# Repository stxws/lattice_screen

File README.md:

玩的点阵屏

hardware：硬件设计
software：软件程序

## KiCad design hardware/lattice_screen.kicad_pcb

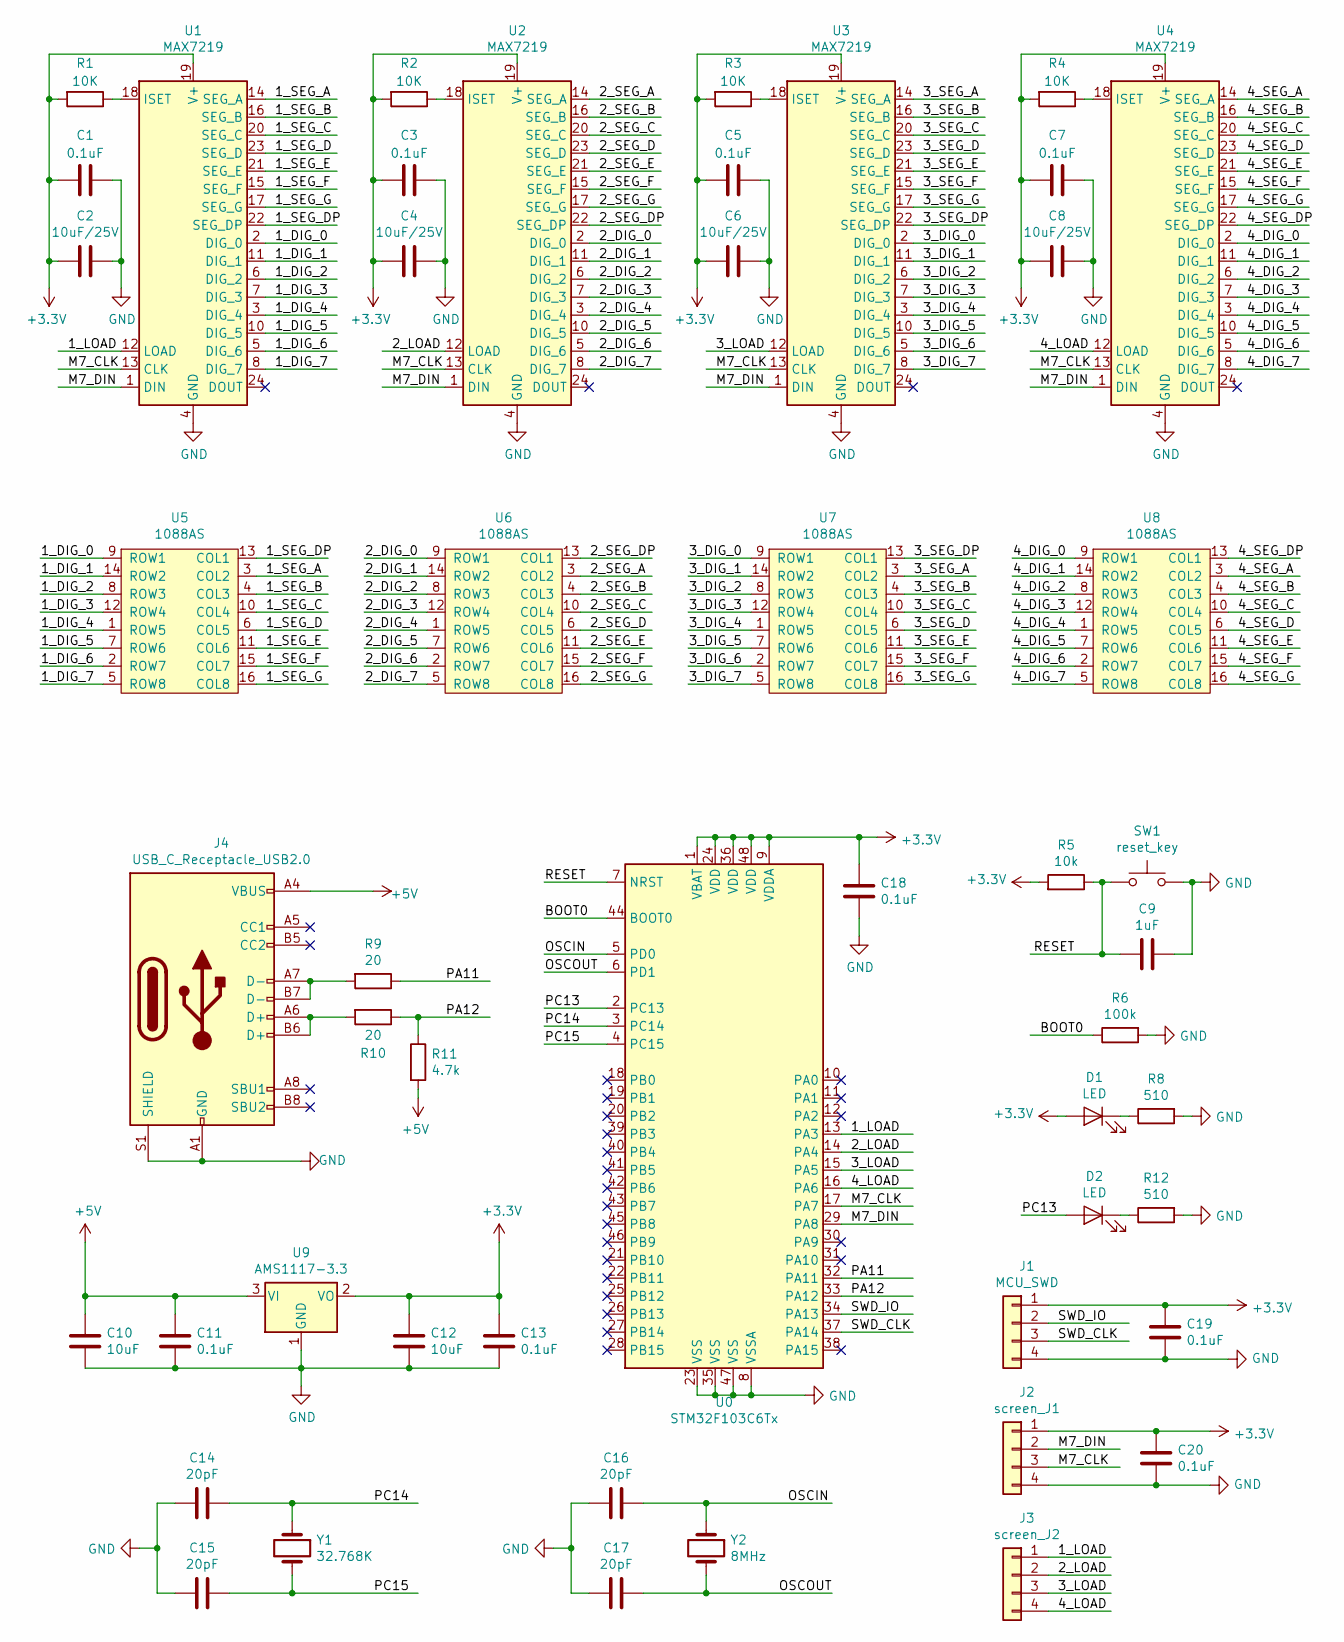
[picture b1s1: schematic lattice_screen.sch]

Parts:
C1, C3, C5, C7, C11, C13, C18, C19, C20: 0.1uF; R_0603_1608Metric_Pad1.05x0.95mm_HandSolder
C2, C4, C6, C8: 10uF/25V; R_0603_1608Metric_Pad1.05x0.95mm_HandSolder
C9: 1uF; R_0603_1608Metric_Pad1.05x0.95mm_HandSolder
C10, C12: 10uF; R_0603_1608Metric_Pad1.05x0.95mm_HandSolder
C14, C15, C16, C17: 20pF; R_0603_1608Metric_Pad1.05x0.95mm_HandSolder
D1, D2: LED; R_0805_2012Metric_Pad1.15x1.40mm_HandSolder
J1: MCU_SWD; PinHeader_1x04_P2.54mm_Horizontal
J2: screen_J1; PinHeader_1x04_P2.54mm_Horizontal
J3: screen_J2; PinHeader_1x04_P2.54mm_Horizontal
J4: USB_C_Receptacle_USB2.0; USB_C_Receptacle_HRO_TYPE-C-31-M-12
R1, R2, R3, R4: 10K; R_0603_1608Metric_Pad1.05x0.95mm_HandSolder
R5: 10k; R_0603_1608Metric_Pad1.05x0.95mm_HandSolder
R6: 100k; R_0603_1608Metric_Pad1.05x0.95mm_HandSolder
R8, R12: 510; R_0603_1608Metric_Pad1.05x0.95mm_HandSolder
R9, R10: 20; R_0603_1608Metric_Pad1.05x0.95mm_HandSolder
R11: 4.7k; R_0603_1608Metric_Pad1.05x0.95mm_HandSolder
SW1: reset_key; SW_SPST_CK_RS282G05A3
U0: STM32F103C6Tx; LQFP-48_7x7mm_P0.5mm
U1, U2, U3, U4: MAX7219; SOP-24_7.5x15.4mm_P1.27mm
U5, U6, U7, U8: 1088AS
U9: AMS1117-3.3; SOT-223-3_TabPin2
Y1: 32.768K; Crystal_DS26_D2.0mm_L6.0mm_Horizontal
Y2: 8MHz; Crystal_HC49-4H_Vertical

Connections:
+3V3: C1.2, C2.2, C3.2, C4.2, C5.2, C6.2, C7.2, C8.2, C12.1, C13.1, C18.1, C19.1, C20.1, D1.2 (A), J1.1, J2.1, R1.2, R2.2, R3.2, R4.2, R5.2, U0.1 (VBAT), U0.9 (VDDA), U0.24 (VDD), U0.36 (VDD), U0.48 (VDD), U1.19 (V+), U2.19 (V+), U3.19 (V+), U4.19 (V+), U9.2 (VO)
+5V: C10.1, C11.1, J4.A4 (VBUS), J4.A9 (VBUS), J4.B4 (VBUS), J4.B9 (VBUS), R11.2, U9.3 (VI)
/1_DIG_0: U1.2 (DIG_0), U5.9 (ROW1)
/1_DIG_1: U1.11 (DIG_1), U5.14 (ROW2)
/1_DIG_2: U1.6 (DIG_2), U5.8 (ROW3)
/1_DIG_3: U1.7 (DIG_3), U5.12 (ROW4)
/1_DIG_4: U1.3 (DIG_4), U5.1 (ROW5)
/1_DIG_5: U1.10 (DIG_5), U5.7 (ROW6)
/1_DIG_6: U1.5 (DIG_6), U5.2 (ROW7)
/1_DIG_7: U1.8 (DIG_7), U5.5 (ROW8)
/1_LOAD: J3.1, U0.13 (PA3), U1.12 (LOAD)
/1_SEG_A: U1.14 (SEG_A), U5.3 (COL2)
/1_SEG_B: U1.16 (SEG_B), U5.4 (COL3)
/1_SEG_C: U1.20 (SEG_C), U5.10 (COL4)
/1_SEG_D: U1.23 (SEG_D), U5.6 (COL5)
/1_SEG_DP: U1.22 (SEG_DP), U5.13 (COL1)
/1_SEG_E: U1.21 (SEG_E), U5.11 (COL6)
/1_SEG_F: U1.15 (SEG_F), U5.15 (COL7)
/1_SEG_G: U1.17 (SEG_G), U5.16 (COL8)
/2_DIG_0: U2.2 (DIG_0), U6.9 (ROW1)
/2_DIG_1: U2.11 (DIG_1), U6.14 (ROW2)
/2_DIG_2: U2.6 (DIG_2), U6.8 (ROW3)
/2_DIG_3: U2.7 (DIG_3), U6.12 (ROW4)
/2_DIG_4: U2.3 (DIG_4), U6.1 (ROW5)
/2_DIG_5: U2.10 (DIG_5), U6.7 (ROW6)
/2_DIG_6: U2.5 (DIG_6), U6.2 (ROW7)
/2_DIG_7: U2.8 (DIG_7), U6.5 (ROW8)
/2_LOAD: J3.2, U0.14 (PA4), U2.12 (LOAD)
/2_SEG_A: U2.14 (SEG_A), U6.3 (COL2)
/2_SEG_B: U2.16 (SEG_B), U6.4 (COL3)
/2_SEG_C: U2.20 (SEG_C), U6.10 (COL4)
/2_SEG_D: U2.23 (SEG_D), U6.6 (COL5)
/2_SEG_DP: U2.22 (SEG_DP), U6.13 (COL1)
/2_SEG_E: U2.21 (SEG_E), U6.11 (COL6)
/2_SEG_F: U2.15 (SEG_F), U6.15 (COL7)
/2_SEG_G: U2.17 (SEG_G), U6.16 (COL8)
/3_DIG_0: U3.2 (DIG_0), U7.9 (ROW1)
/3_DIG_1: U3.11 (DIG_1), U7.14 (ROW2)
/3_DIG_2: U3.6 (DIG_2), U7.8 (ROW3)
/3_DIG_3: U3.7 (DIG_3), U7.12 (ROW4)
/3_DIG_4: U3.3 (DIG_4), U7.1 (ROW5)
/3_DIG_5: U3.10 (DIG_5), U7.7 (ROW6)
/3_DIG_6: U3.5 (DIG_6), U7.2 (ROW7)
/3_DIG_7: U3.8 (DIG_7), U7.5 (ROW8)
/3_LOAD: J3.3, U0.15 (PA5), U3.12 (LOAD)
/3_SEG_A: U3.14 (SEG_A), U7.3 (COL2)
/3_SEG_B: U3.16 (SEG_B), U7.4 (COL3)
/3_SEG_C: U3.20 (SEG_C), U7.10 (COL4)
/3_SEG_D: U3.23 (SEG_D), U7.6 (COL5)
/3_SEG_DP: U3.22 (SEG_DP), U7.13 (COL1)
/3_SEG_E: U3.21 (SEG_E), U7.11 (COL6)
/3_SEG_F: U3.15 (SEG_F), U7.15 (COL7)
/3_SEG_G: U3.17 (SEG_G), U7.16 (COL8)
/4_DIG_0: U4.2 (DIG_0), U8.9 (ROW1)
/4_DIG_1: U4.11 (DIG_1), U8.14 (ROW2)
/4_DIG_2: U4.6 (DIG_2), U8.8 (ROW3)
/4_DIG_3: U4.7 (DIG_3), U8.12 (ROW4)
/4_DIG_4: U4.3 (DIG_4), U8.1 (ROW5)
/4_DIG_5: U4.10 (DIG_5), U8.7 (ROW6)
/4_DIG_6: U4.5 (DIG_6), U8.2 (ROW7)
/4_DIG_7: U4.8 (DIG_7), U8.5 (ROW8)
/4_LOAD: J3.4, U0.16 (PA6), U4.12 (LOAD)
/4_SEG_A: U4.14 (SEG_A), U8.3 (COL2)
/4_SEG_B: U4.16 (SEG_B), U8.4 (COL3)
/4_SEG_C: U4.20 (SEG_C), U8.10 (COL4)
/4_SEG_D: U4.23 (SEG_D), U8.6 (COL5)
/4_SEG_DP: U4.22 (SEG_DP), U8.13 (COL1)
/4_SEG_E: U4.21 (SEG_E), U8.11 (COL6)
/4_SEG_F: U4.15 (SEG_F), U8.15 (COL7)
/4_SEG_G: U4.17 (SEG_G), U8.16 (COL8)
/BOOT0: R6.1, U0.44 (BOOT0)
/M7_CLK: J2.3, U0.17 (PA7), U1.13 (CLK), U2.13 (CLK), U3.13 (CLK), U4.13 (CLK)
/M7_DIN: J2.2, U0.29 (PA8), U1.1 (DIN), U2.1 (DIN), U3.1 (DIN), U4.1 (DIN)
/OSCIN: C16.1, U0.5 (PD0), Y2.1
/OSCOUT: C17.1, U0.6 (PD1), Y2.2
/PA11: R9.1, U0.32 (PA11)
/PA12: R10.1, R11.1, U0.33 (PA12)
/PC13: D2.2 (A), U0.2 (PC13)
/PC14: C14.1, U0.3 (PC14), Y1.1
/PC15: C15.1, U0.4 (PC15), Y1.2
/RESET: C9.2, R5.1, SW1.2, U0.7 (NRST)
/SWD_CLK: J1.3, U0.37 (PA14)
/SWD_IO: J1.2, U0.34 (PA13)
GND: C1.1, C2.1, C3.1, C4.1, C5.1, C6.1, C7.1, C8.1, C9.1, C10.2, C11.2, C12.2, C13.2, C14.2, C15.2, C16.2, C17.2, C18.2, C19.2, C20.2, J1.4, J2.4, J4.A1 (GND), J4.A12 (GND), J4.B1 (GND), J4.B12 (GND), J4.S1 (SHIELD), R6.2, R8.2, R12.2, SW1.1, U0.8 (VSSA), U0.23 (VSS), U0.35 (VSS), U0.47 (VSS), U1.4 (GND), U1.9 (GND), U2.4 (GND), U2.9 (GND), U3.4 (GND), U3.9 (GND), U4.4 (GND), U4.9 (GND), U9.1 (GND)
unnamed: D1.1 (K), R8.1
unnamed: D2.1 (K), R12.1
unnamed: J4.A6 (D+), J4.B6 (D+), R10.2
unnamed: J4.A7 (D-), J4.B7 (D-), R9.2
unnamed: R1.1, U1.18 (ISET)
unnamed: R2.1, U2.18 (ISET)
unnamed: R3.1, U3.18 (ISET)
unnamed: R4.1, U4.18 (ISET)

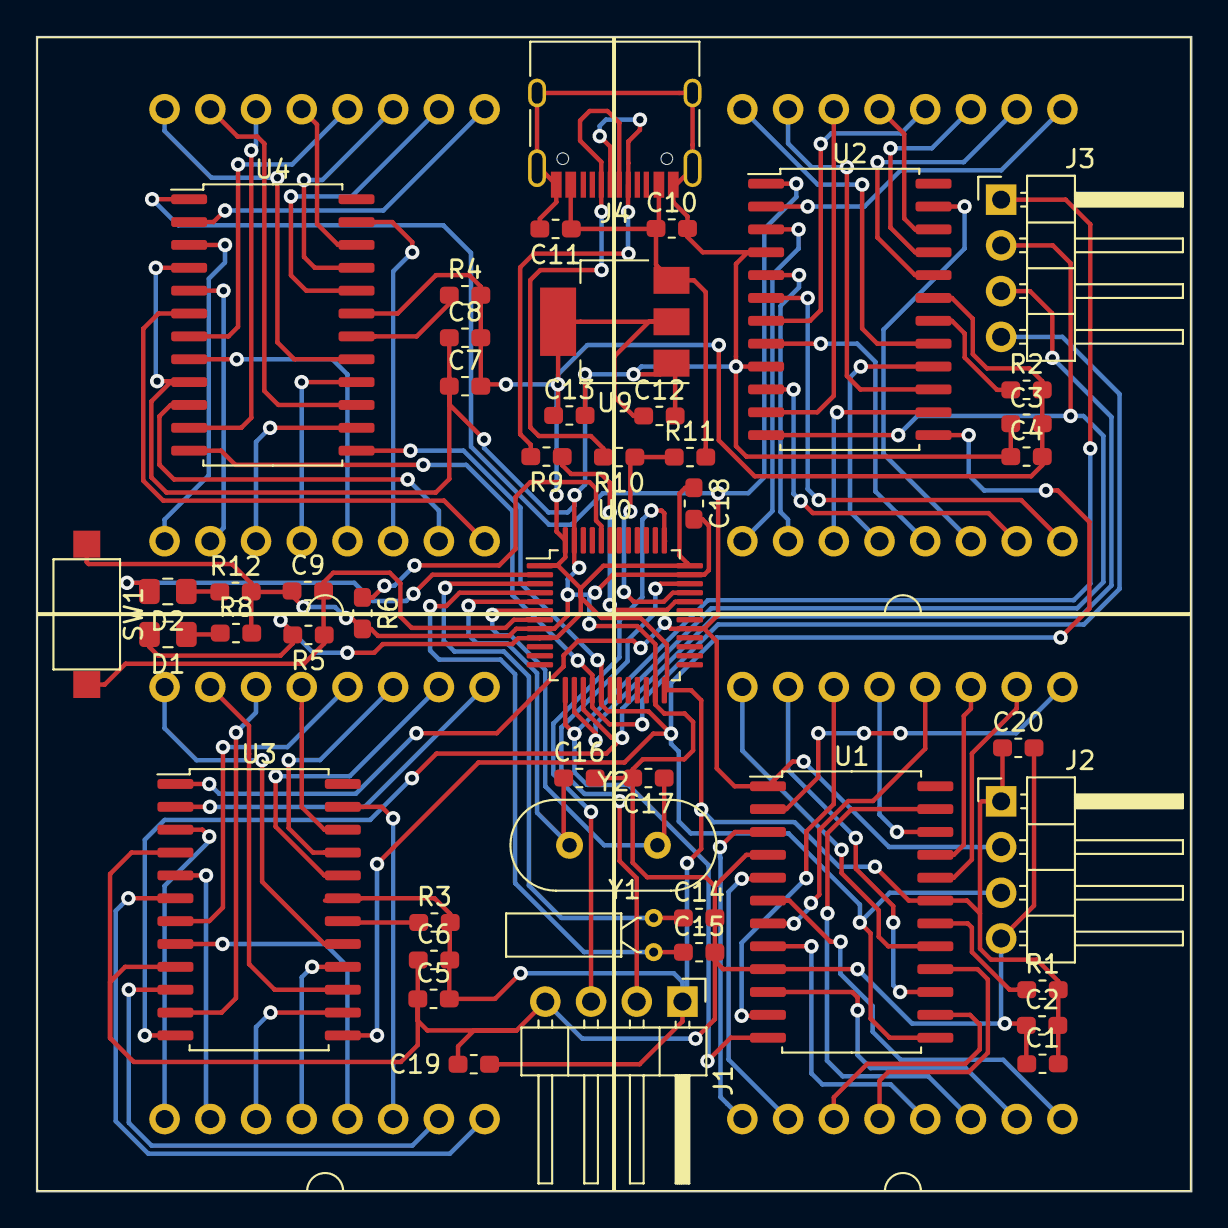
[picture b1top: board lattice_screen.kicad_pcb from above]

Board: 2 copper layers, 64.2 x 64.2 mm, 50 parts (0 on the bottom side), 92 nets.

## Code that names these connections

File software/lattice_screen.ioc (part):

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PA6.GPIOParameters=GPIO_PuPd
PA10.Mode=Asynchronous
Mcu.UserName=STM32F103C6Tx
PC13-TAMPER-RTC.GPIOParameters=PinState,GPIO_PuPd,GPIO_ModeDefaultOutputPP
PA3.GPIO_PuPd=GPIO_PULLUP
PC13-TAMPER-RTC.Signal=GPIO_Output
PA3.GPIOParameters=GPIO_PuPd
PA13.Signal=SYS_JTMS-SWDIO
PA9.Mode=Asynchronous
PA9.Signal=USART1_TX
PA8.GPIOParameters=GPIO_PuPd
PA7.GPIO_PuPd=GPIO_PULLUP
PA5.Signal=GPIO_Output
PA4.GPIO_PuPd=GPIO_PULLUP
board=custom
PA6.GPIO_PuPd=GPIO_PULLUP
PC13-TAMPER-RTC.PinState=GPIO_PIN_RESET
PA14.Mode=Serial_Wire
PA5.GPIO_PuPd=GPIO_PULLUP
PA8.Signal=GPIO_Output
PA4.GPIOParameters=GPIO_PuPd
PA13.Mode=Serial_Wire
Mcu.Name=STM32F103C(4-6)Tx
PA4.Signal=GPIO_Output
PC13-TAMPER-RTC.GPIO_ModeDefaultOutputPP=GPIO_MODE_OUTPUT_PP
Mcu.Package=LQFP48
PA6.Signal=GPIO_Output
PC13-TAMPER-RTC.GPIO_PuPd=GPIO_PULLUP
PA10.Signal=USART1_RX
PA14.Signal=SYS_JTCK-SWCLK
PA5.GPIOParameters=GPIO_PuPd
PA8.GPIO_PuPd=GPIO_PULLUP
PA7.GPIOParameters=GPIO_PuPd
PA3.Signal=GPIO_Output
PA7.Signal=GPIO_Output

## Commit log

2022-03-18 init
